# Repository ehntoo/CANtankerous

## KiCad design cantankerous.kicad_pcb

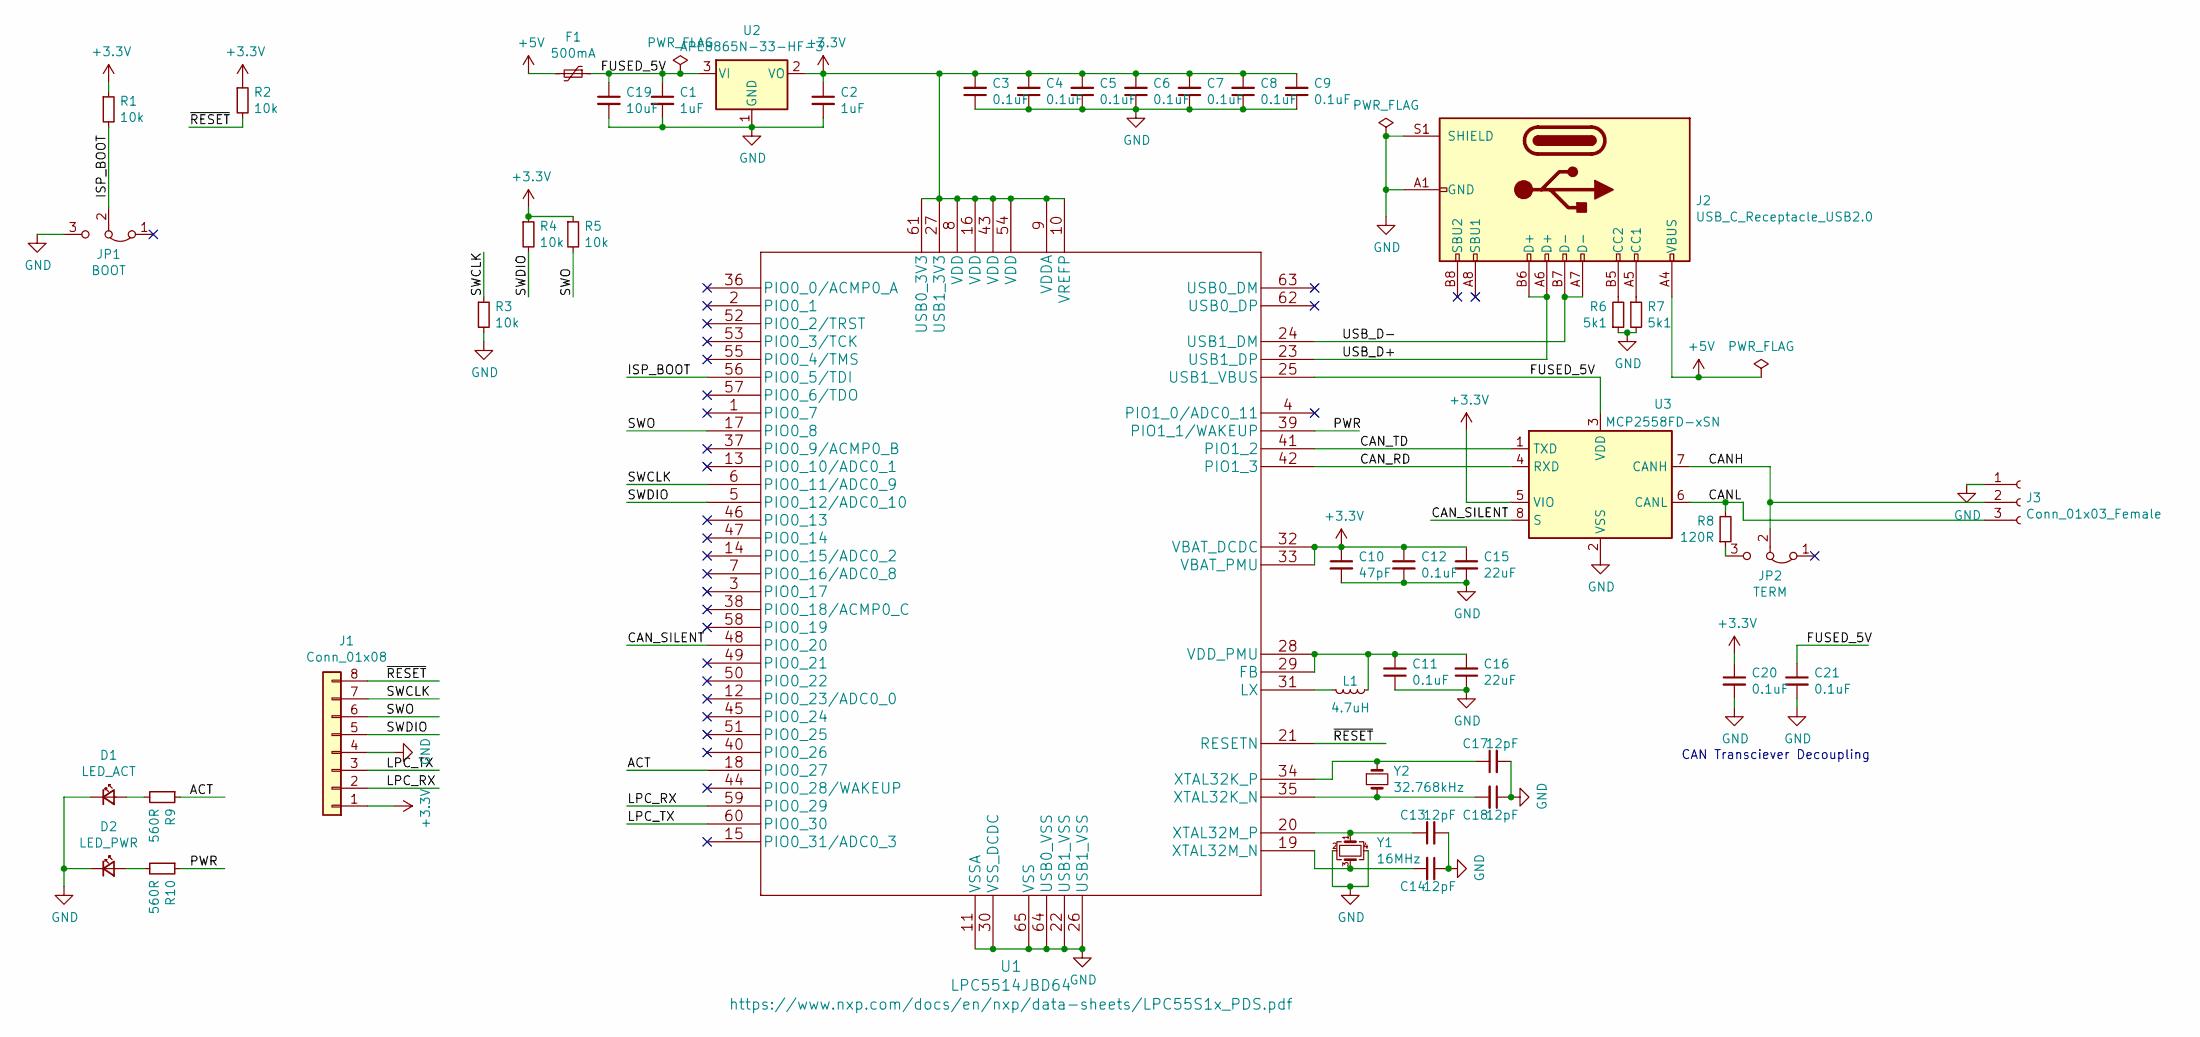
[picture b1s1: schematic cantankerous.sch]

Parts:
C1, C2: 1uF; C_0603_1608Metric_Pad1.08x0.95mm_HandSolder
C3, C4, C5, C6, C7, C8, C9, C11, C12, C20, C21: 0.1uF; C_0402_1005Metric_Pad0.74x0.62mm_HandSolder
C10: 47pF; C_0402_1005Metric_Pad0.74x0.62mm_HandSolder
C13, C14, C17, C18: 12pF; C_0402_1005Metric_Pad0.74x0.62mm_HandSolder
C15, C16: 22uF; C_0805_2012Metric_Pad1.18x1.45mm_HandSolder
C19: 10uF; C_0805_2012Metric_Pad1.18x1.45mm_HandSolder
D1: LED_ACT; D_0603_1608Metric_Pad1.05x0.95mm_HandSolder
D2: LED_PWR; D_0603_1608Metric_Pad1.05x0.95mm_HandSolder
F1: 500mA; Fuse_0805_2012Metric_Pad1.15x1.40mm_HandSolder
J1: Conn_01x08; SOIC_clipProgSmall
J2: USB_C_Receptacle_USB2.0; USB_C_Receptacle_HRO_TYPE-C-31-M-12
J3: Conn_01x03_Female; TerminalBlock_Phoenix_MKDS-1,5-3_1x03_P5.00mm_Horizontal
JP1: BOOT; PinHeader_1x03_P2.54mm_Vertical
JP2: TERM; PinHeader_1x03_P2.54mm_Vertical
L1: 4.7uH; L_0805_2012Metric_Pad1.15x1.40mm_HandSolder
R1, R2, R3, R4, R5: 10k; R_0402_1005Metric_Pad0.72x0.64mm_HandSolder
R6, R7: 5k1; R_0402_1005Metric_Pad0.72x0.64mm_HandSolder
R8: 120R; R_0603_1608Metric_Pad0.98x0.95mm_HandSolder
R9, R10: 560R; R_0402_1005Metric_Pad0.72x0.64mm_HandSolder
U1: LPC5514JBD64
U2: APE8865N-33-HF-3; SOT-23
U3: MCP2558FD-xSN; SOIC-8_3.9x4.9mm_P1.27mm
Y1: 16MHz; Crystal_SMD_3225-4Pin_3.2x2.5mm
Y2: 32.768kHz; Crystal_DS26_D2.0mm_L6.0mm_Horizontal

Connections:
+3V3: C2.1, C3.2, C4.2, C5.2, C6.2, C7.2, C8.2, C9.2, C10.1, C12.1, C15.1, C20.1, J1.1, R1.1, R2.1, R4.1, R5.1, U1.8 (VDD), U1.9 (VDDA), U1.10 (VREFP), U1.16 (VDD), U1.27 (USB1_3V3), U1.32 (VBAT_DCDC), U1.33 (VBAT_PMU), U1.43 (VDD), U1.54 (VDD), U1.61 (USB0_3V3), U2.2 (VO), U3.5 (VIO)
+5V: F1.2, J2.A4 (VBUS), J2.A9 (VBUS), J2.B4 (VBUS), J2.B9 (VBUS)
/ACT: R9.1, U1.18 (PIO0_27)
/CANH: J3.2, JP2.2 (C), U3.7 (CANH)
/CANL: J3.3, R8.2, U3.6 (CANL)
/CAN_RD: U1.42 (PIO1_3), U3.4 (RXD)
/CAN_SILENT: U1.48 (PIO0_20), U3.8 (S)
/CAN_TD: U1.41 (PIO1_2), U3.1 (TXD)
/FUSED_5V: C1.1, C19.1, C21.1, F1.1, U1.25 (USB1_VBUS), U2.3 (VI), U3.3 (VDD)
/ISP_BOOT: JP1.2 (C), R1.2, U1.56 (PIO0_5/TDI)
/LPC_RX: J1.2, U1.59 (PIO0_29)
/LPC_TX: J1.3, U1.60 (PIO0_30)
/PWR: R10.1, U1.39 (PIO1_1/WAKEUP)
/SWCLK: J1.7, R3.1, U1.6 (PIO0_11/ADC0_9)
/SWDIO: J1.5, R4.2, U1.5 (PIO0_12/ADC0_10)
/SWO: J1.6, R5.2, U1.17 (PIO0_8)
/USB_D+: J2.A6 (D+), J2.B6 (D+), U1.23 (USB1_DP)
/USB_D-: J2.A7 (D-), J2.B7 (D-), U1.24 (USB1_DM)
/~RESET: J1.8, R2.2, U1.21 (RESETN)
GND: C1.2, C2.2, C3.1, C4.1, C5.1, C6.1, C7.1, C8.1, C9.1, C10.2, C11.1, C12.2, C13.2, C14.1, C15.2, C16.1, C17.2, C18.1, C19.2, C20.2, C21.2, D1.1 (K), D2.1 (K), J1.4, J2.A1 (GND), J2.A12 (GND), J2.B1 (GND), J2.B12 (GND), J2.S1 (SHIELD), J3.1, JP1.3 (B), R3.2, R6.1, R7.2, U1.11 (VSSA), U1.22 (USB1_VSS), U1.26 (USB1_VSS), U1.30 (VSS_DCDC), U1.64 (USB0_VSS), U1.65 (VSS), U2.1 (GND), U3.2 (VSS), Y1.2, Y1.4
unnamed: C11.2, C16.2, L1.2, U1.28 (VDD_PMU), U1.29 (FB)
unnamed: C13.1, U1.20 (XTAL32M_P), Y1.1
unnamed: C14.2, U1.19 (XTAL32M_N), Y1.3
unnamed: C17.1, U1.34 (XTAL32K_P), Y2.1
unnamed: C18.2, U1.35 (XTAL32K_N), Y2.2
unnamed: D1.2 (A), R9.2
unnamed: D2.2 (A), R10.2
unnamed: J2.A5 (CC1), R7.1
unnamed: J2.B5 (CC2), R6.2
unnamed: JP2.3 (B), R8.1
unnamed: L1.1, U1.31 (LX)

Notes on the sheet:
CAN Transciever Decoupling

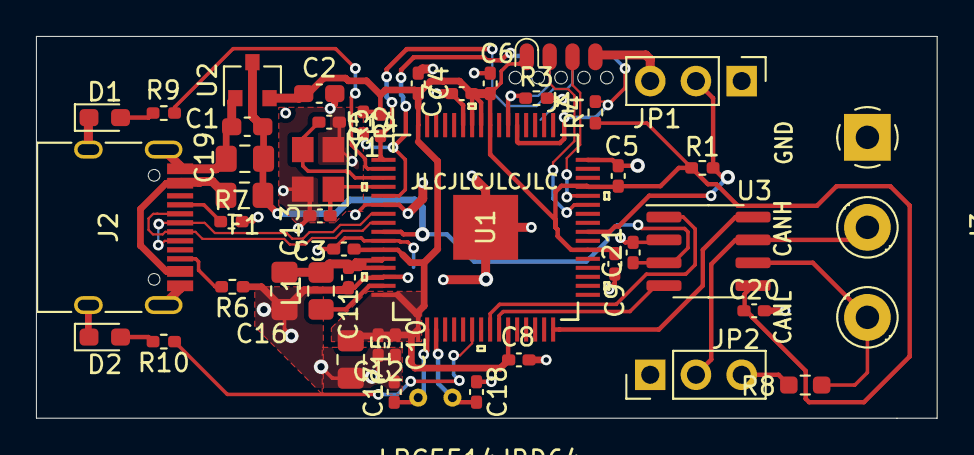
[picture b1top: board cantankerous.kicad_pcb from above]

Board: 2 copper layers, 50.0 x 21.2 mm, 45 parts (1 on the bottom side), 31 nets.

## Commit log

2020-12-03 Initial Commit
    Pulled in symbols/footprints from the NXP Ultra Librarian file.
2020-12-05 Well, that was a lot of work. Rev 0.1
2020-12-05 Add r01 production gerbers
2020-12-05 Add license - Solderpad 2.1
2020-12-05 Ignore some kicad temp files
2020-12-05 Update L1 footprint and value to fix units
2020-12-18 Initial design revisions from r0.1
    Actually connect VCC to the LPC5514 DCDC converter input (lol)
    Add decoupling caps to CAN transciever (layout not presently ideal)
    Rearrange activity LED trace to improve ground plane continuity
2020-12-20 Significant board layout revisions
    Clean up a number of current return paths for the high-speed USB
    and CAN-FD signals
2020-12-21 New DCDC converter layout
2020-12-25 Migrate to a SOICbite debug connector
    Saves a bunch of mess on the ground plane, and I also managed to
    cram all the components onto the topside

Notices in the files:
parts and their libraries:
Copyright 2016 Accelerated Designs. All rights reserved.
